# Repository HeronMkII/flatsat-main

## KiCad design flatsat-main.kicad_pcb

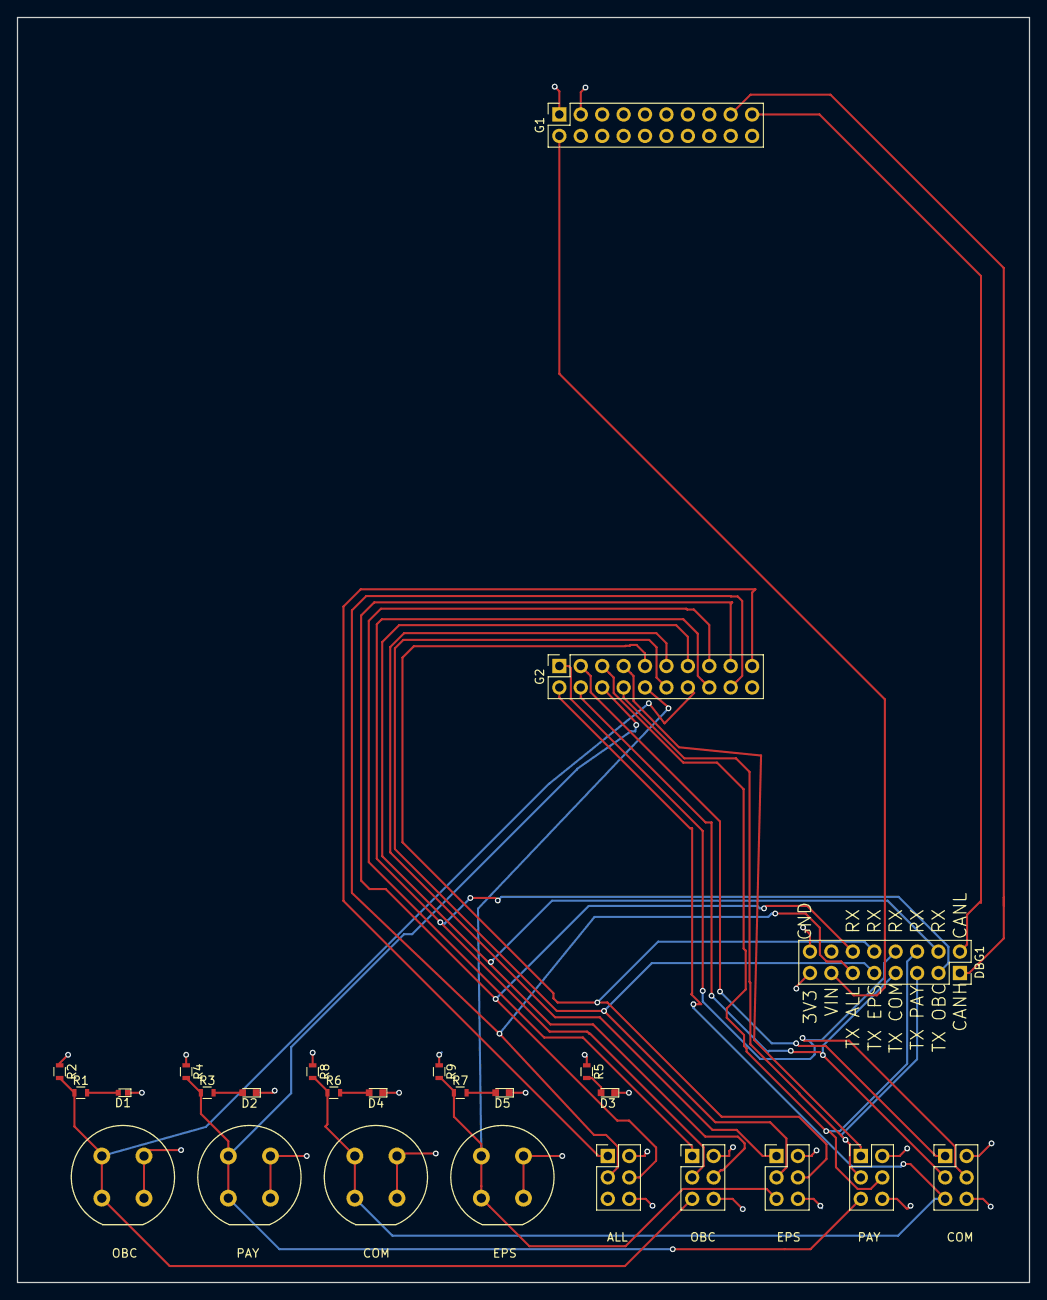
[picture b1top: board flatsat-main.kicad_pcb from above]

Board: 4 copper layers, 120.0 x 150.0 mm, 26 parts (0 on the bottom side), 29 nets.

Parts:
ALL: PGM_ALL; Pin_Header_Straight_2x03_Pitch2.54mm
COM: COM_PGM; Pin_Header_Straight_2x03_Pitch2.54mm
COM#2: RST_COM; Push_E-Switch_KS01Q01
D1: LED; LED_0402
D2, D3, D4, D5: LED; LED_0603
DBG1: CONN_02X08; Socket_Strip_Straight_2x08_Pitch2.54mm
EPS: EPS_PGM; Pin_Header_Straight_2x03_Pitch2.54mm
EPS#2: RST_EPS; Push_E-Switch_KS01Q01
G1, G2: CONN_02X10; Socket_Strip_Straight_2x10_Pitch2.54mm
OBC: OBC_PGM; Pin_Header_Straight_2x03_Pitch2.54mm
OBC#2: RST_OBC; Push_E-Switch_KS01Q01
PAY: PAY_PGM; Pin_Header_Straight_2x03_Pitch2.54mm
PAY#2: RST_PAY; Push_E-Switch_KS01Q01
R1, R2, R3, R4, R5, R6, R7, R8, R9: R_Small; R_0603

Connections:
/3V3CRIT: ALL.2, COM.2, DBG1.15, EPS.2, G1.1, OBC.2, PAY.2, R2.1, R4.1, R5.1, R8.1, R9.1
/CANH: DBG1.1, G1.17
/CANL: DBG1.2, G1.19
/COM_MISO_A: COM.1, G2.3
/COM_MOSI_A: COM.4, DBG1.8, G2.1
/COM_RST: COM.5, COM#2.1, COM#2.3, G2.2, R6.1, R8.2
/COM_SCK_A: COM.3, DBG1.7, G2.4
/EPS_MISO_A: EPS.1, G2.11
/EPS_MOSI_A: DBG1.10, EPS.4, G2.9
/EPS_RST: EPS.5, EPS#2.1, EPS#2.3, G2.10, R7.1, R9.2
/EPS_SCK_A: DBG1.9, EPS.3, G2.12
/MISO_A_COMMON: ALL.1, G2.19
/MOSI_A_COMMON: ALL.4, DBG1.12, G2.17
/OBC_MISO_A: G2.15, OBC.1
/OBC_MOSI_A: DBG1.4, G2.13, OBC.4
/OBC_RST: G2.14, OBC.5, OBC#2.1, OBC#2.3, R1.1, R2.2
/OBC_SCK_A: DBG1.3, G2.16, OBC.3
/PAY_MISO_A: G2.7, PAY.1
/PAY_MOSI_A: DBG1.6, G2.5, PAY.4
/PAY_RST: G2.6, PAY.5, PAY#2.1, PAY#2.3, R3.1, R4.2
/PAY_SCK_A: DBG1.5, G2.8, PAY.3
/SCK_A_COMMON: ALL.3, DBG1.11, G2.18
/VIN: DBG1.13, G1.2
GND: ALL.6, COM.6, COM#2.2, COM#2.4, D1.1, D2.1, D3.1, D4.1, D5.1, DBG1.16, EPS.6, EPS#2.2, EPS#2.4, G1.3, OBC.6, OBC#2.2, OBC#2.4, PAY.6, PAY#2.2, PAY#2.4
unnamed: D1.2, R1.2
unnamed: D2.2, R3.2
unnamed: D3.2, R5.2
unnamed: D4.2, R6.2
unnamed: D5.2, R7.2

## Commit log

2017-08-21 new main board
    ...
2017-08-21 done
    wohoo
2017-08-21 Added gerber outputs.
2017-09-02 Modified outputs for manufacture.
